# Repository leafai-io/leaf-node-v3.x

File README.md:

# Leaf Node 3.1

Leaf AI is an independent, open-source project. If you find it useful, you can support its continued development at [Leaf AI Support](https://leafai.io/support.html).

The Leaf Node is an open-source environmental 
monitoring and control device built on the 
ESP32-S3. It reads sensor data, publishes it 
over MQTT, and can trigger actuators — allowing 
you to monitor conditions and directly control 
connected devices such as lights, fans, pumps 
and valves. Configuration is handled wirelessly 
via BLE, making it a self-contained building 
block for precision agriculture and 
environmental monitoring and automation systems.

<!-- Hero image: replace the path below with your device photo -->
<!--  -->

---

## Philosophy

Leaf Node is built around one principle: **it should just work.** From first flash to live sensor data in minutes — simple enough for a grower to deploy in the field, open enough for a developer to extend and build on. No unnecessary complexity, no steep learning curve.

---

## Features

- **Multi-protocol sensor support** — I2C, RS485, SDI-12, OneWire on a single board
- **MQTT telemetry** — publishes sensor data and heartbeats, receives commands
- **OTA firmware updates** — triggered via MQTT command, no physical access needed
- **BLE provisioning** — initial Wi-Fi and MQTT setup from the companion app, no serial cable required
- **Scheduling** — DAC and actuator outputs can be programmed on a time-based schedule
- **Smart control** — MOSFET and relay outputs with duration-based switching
- **Node chaining** — UART-based daisy-chain for multi-node deployments
- **Watchdog & health monitoring** — automatic recovery with exponential backoff on sensor errors
- **Factory mode** — serial-console provisioning for production flashing

---

## Hardware

### Overview

| Component | Details |
|-----------|---------|
| MCU | ESP32-S3 |
| Status LED | WS2812B addressable RGB (v3) |
| RS485 | Half-duplex, DE/RE controlled |
| I2C | SDA GPIO8, SCL GPIO9 |
| SDI-12 | GPIO12 (shared with OneWire via hardware bridge) |
| OneWire | GPIO12 |
| Actuators | MOSFET (GPIO36), Relay (GPIO38), DAC (MCP4725 via I2C) |
| PWM | GPIO2 (1 kHz, 10-bit) + MOSFET gate (5 kHz, 10-bit) |

### Supported Sensors

| Sensor | Interface | Wiring | Measurement |
|--------|-----------|--------|-------------|
| SHT31  | I2C (0x44) | +3.3V · GND · SDA · SCL | Temperature, Humidity |
| EZO pH | I2C (0x63) | +3.3V · GND · SDA · SCL | pH |
| EZO EC | I2C (0x64) | +3.3V · GND · SDA · SCL | Electrical Conductivity |
| TEROS 12 | SDI-12 | +3.3V · GND · SDI-12 | Soil moisture, temperature, EC |
| DS18B20 | OneWire | +3.3V · GND · Need Modification | Temperature |
| SLT5007 | RS485 | +3.3V · GND · A · B | VWC, Bulk EC, Soil temperature, Pore EC |
| CWT-PSS | RS485 | +12V · GND · A · B | PAR (Photosynthetically Active Radiation) |
| LEAFTHSN | RS485 | +12V · GND · A · B | Leaf wetness, Leaf temperature |
| CWT-SoilTHS | RS485 | +12V · GND · A · B | VWC, Soil temperature |
| CWT-THXXS | RS485 | +12V · GND · A · B | Air temperature, Humidity, VPD |

### Actuators

| Actuator | GPIO / Interface | Wiring | Typical Use |
|----------|-----------------|--------|-------------|
| MOSFET | GPIO36 | +12V · -PWR | Pumps, fans, DC loads |
| Relay | GPIO38 | COM · NO · NC | AC/DC switching, high-current loads |
| DAC (MCP4725) | I2C (0x60) | 0-10V · GND | Analog 0–5 V output (e.g. dosing pumps) |
| PWM | GPIO2 | IO2 · GND | Variable speed / dimming control |

### PCB & Enclosure

- KiCad project: [hardware/pcb/kiCad/](hardware/pcb/kiCad/)
- Enclosure STL/STEP files: [hardware/enclosure/](hardware/enclosure/)
---

## Getting Started

### Option A — Web Flasher (recommended)

No toolchain required. Works directly in Chrome/Edge.

1. **Get the hardware** — order a ready-to-use Leaf Node at [Build Your Leaf Node](https://leafai.io/build-node.html), or fabricate your own PCB from the [KiCad files](hardware/pcb/kiCad/)
2. Open the **[Leaf AI Firmware Flasher](https://leafai.io/firmware-flasher.html)** and follow the on-screen steps
3. Open the Leaf AI app, tap **Add Device**, and provision Wi-Fi via BLE

That's it — the node connects to the Leaf AI backend and starts publishing sensor data.

> A free Leaf AI account is required to use the app. Sign up directly in the Leaf AI app.

---

### Option B — Build from source (PlatformIO)

For developers who want to modify or extend the firmware.

**Prerequisites:** [PlatformIO](https://platformio.org/) (CLI or VS Code extension)

#### 1. Assemble the hardware

Fabricate the PCB from the files in [hardware/pcb/](hardware/pcb/) and wire your sensors according to the pin table above.

#### 2. Flash the firmware

> **First flash:** Use the **[Leaf AI Firmware Flasher](https://leafai.io/firmware-flasher.html)** for the initial flash. It writes a compatible serial number to the device that is required for communication with the Leaf AI app. Subsequent builds can be uploaded via PlatformIO.

```bash
git clone https://github.com/leafai-io/leaf-node-v3.1.git
cd leaf-node-v3.1
pio run --target upload
```

Monitor serial output (115200 baud):

```bash
pio device monitor
```

#### 3. Provision via BLE

Open the Leaf AI app, tap **Add Device**, and follow the on-screen steps to configure Wi-Fi and link your account.

---

## Using with the App

Once your Leaf Node is provisioned, open the Leaf AI app to view live sensor readings, configure schedules, and control actuators — all from your phone.

---

## License

This project uses two open-source licences depending on what you are working with:

| Component | Licence |
|-----------|---------|
| Firmware / Software | [GNU AGPL-3.0](licenses/LICENSE-SOFTWARE) |
| Hardware (PCB, enclosure) | [CERN-OHL-S v2](licenses/LICENSE-HARDWARE) |

**Software (AGPL-3.0):** You can use, modify, and distribute the firmware freely, but any modified version you run as a networked service must also be released under the same licence.

**Hardware (CERN-OHL-S v2):** You can study, modify, and manufacture the hardware freely, but any modified design you distribute or produce must be released under the same licence with complete source files.

**If you create a fork, we'd love to hear about it.** Open an issue or send us a message so we can showcase your project and potentially integrate useful improvements.

---

## Support

Leaf AI is an independent, open-source project. If you find it useful, you can support its continued development at [Leaf AI Support](https://leafai.io/support.html).

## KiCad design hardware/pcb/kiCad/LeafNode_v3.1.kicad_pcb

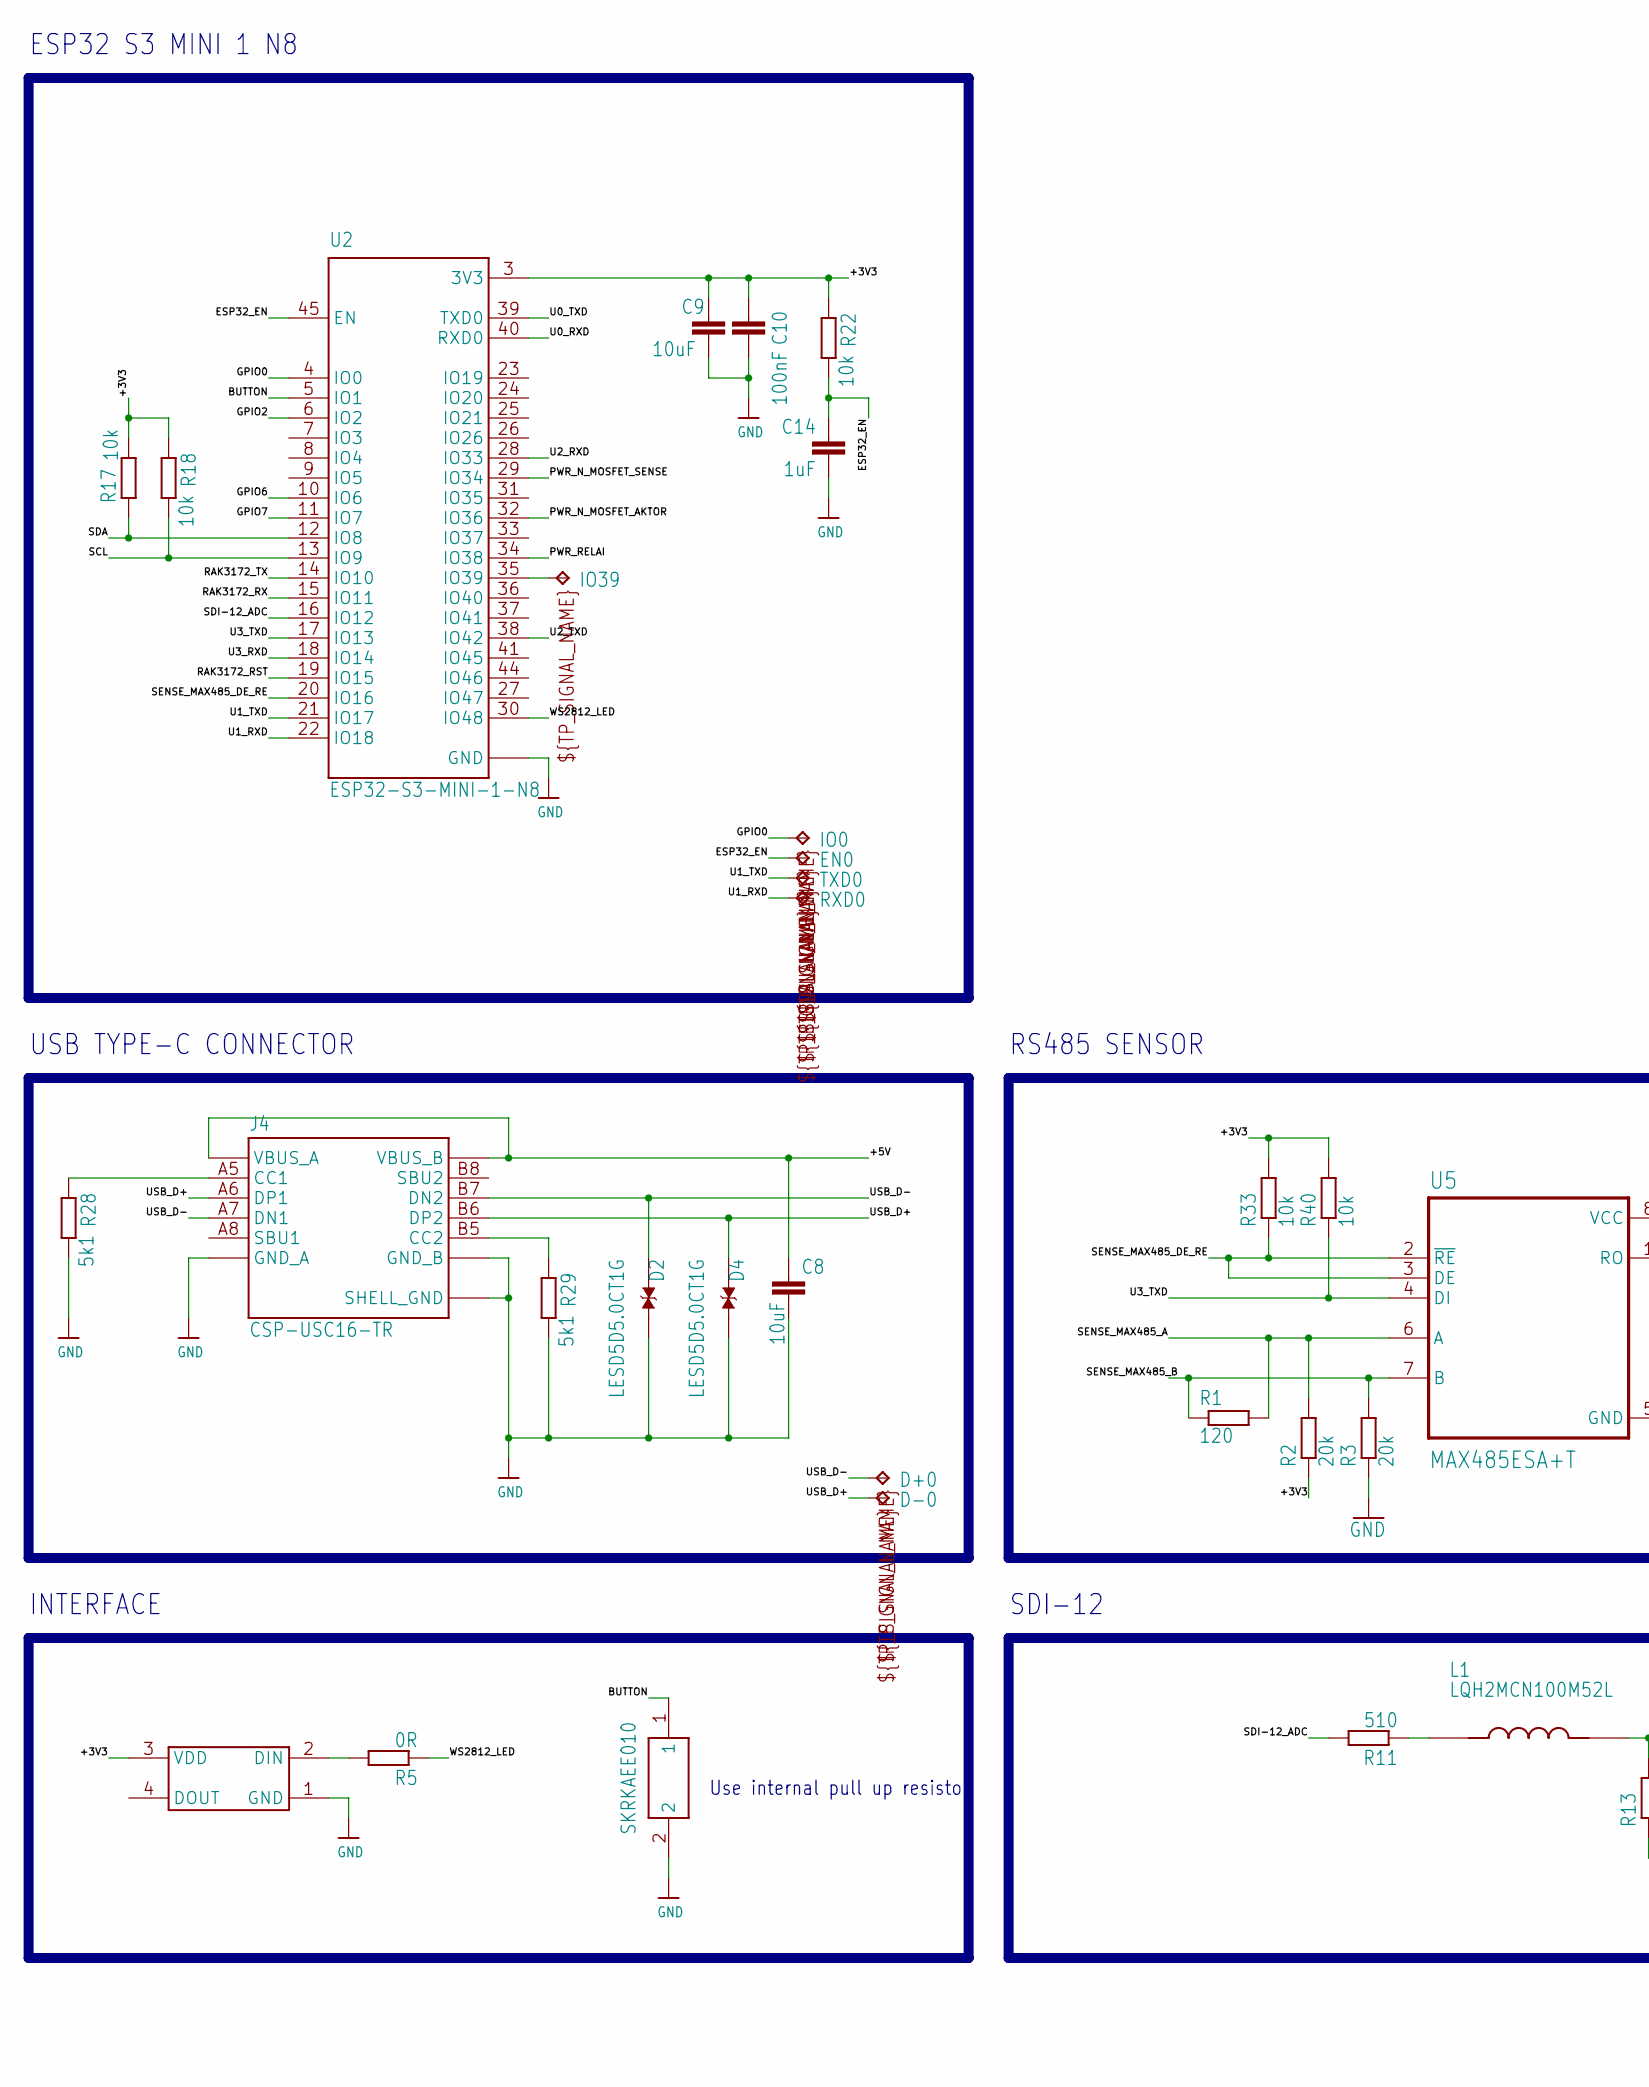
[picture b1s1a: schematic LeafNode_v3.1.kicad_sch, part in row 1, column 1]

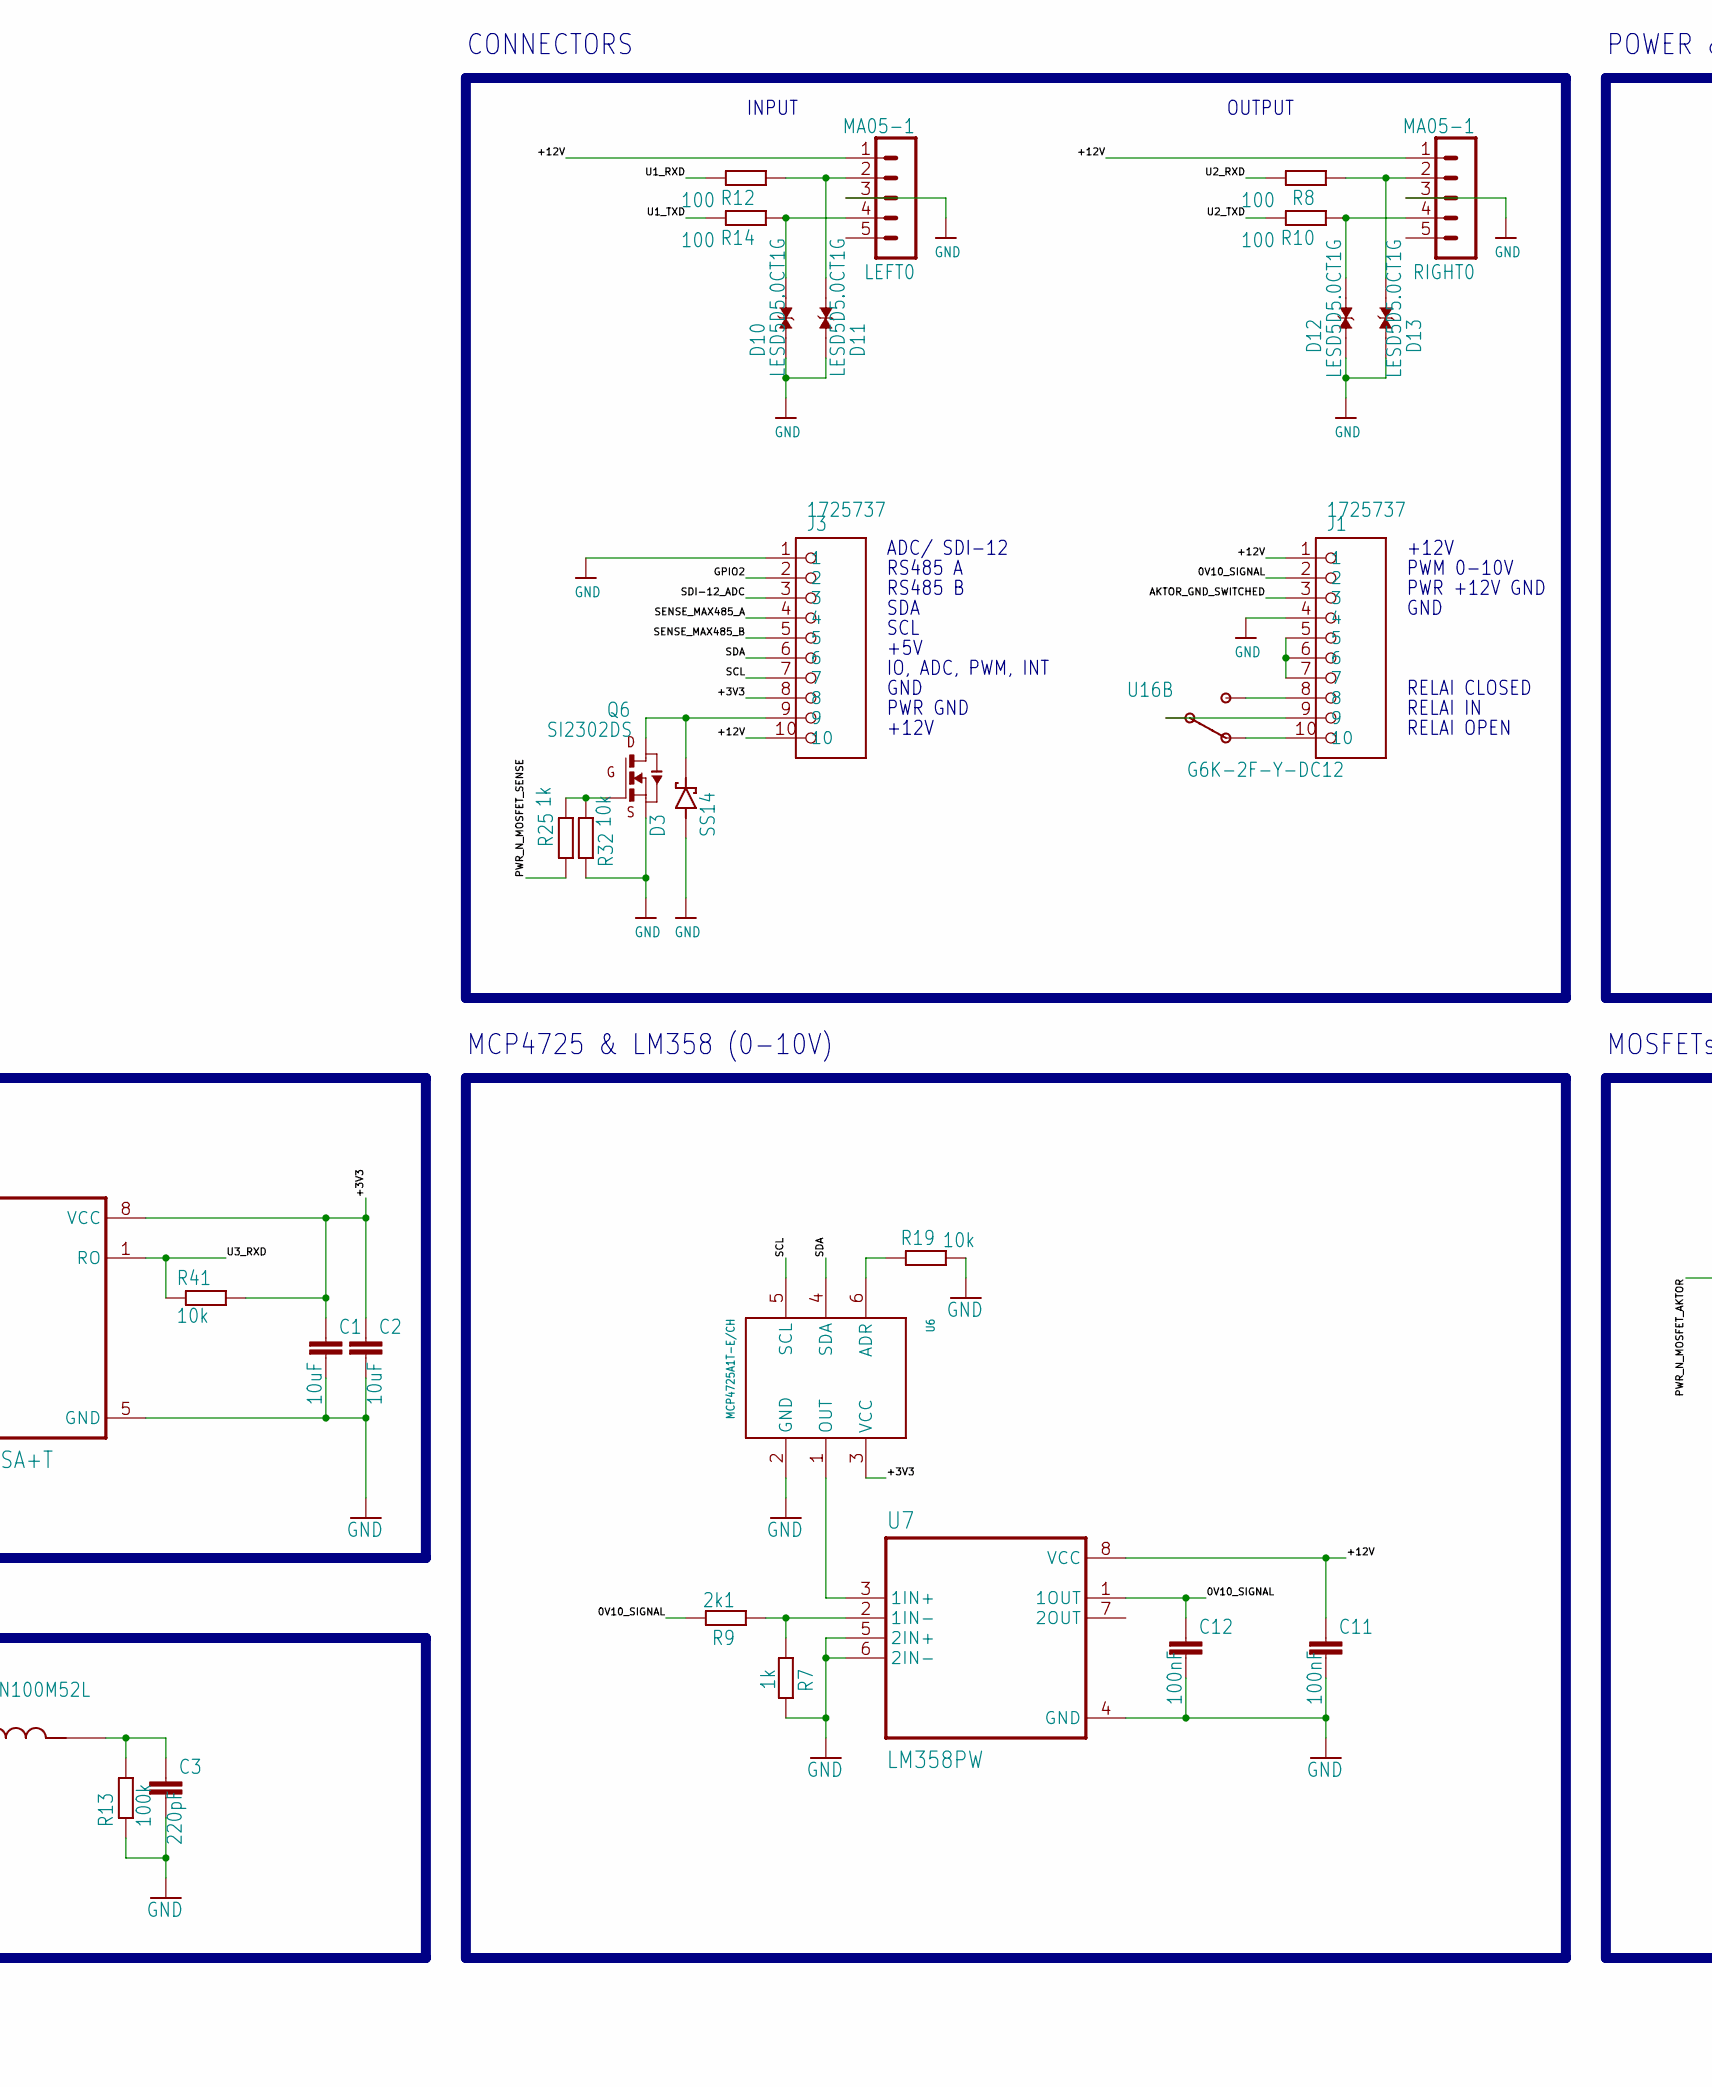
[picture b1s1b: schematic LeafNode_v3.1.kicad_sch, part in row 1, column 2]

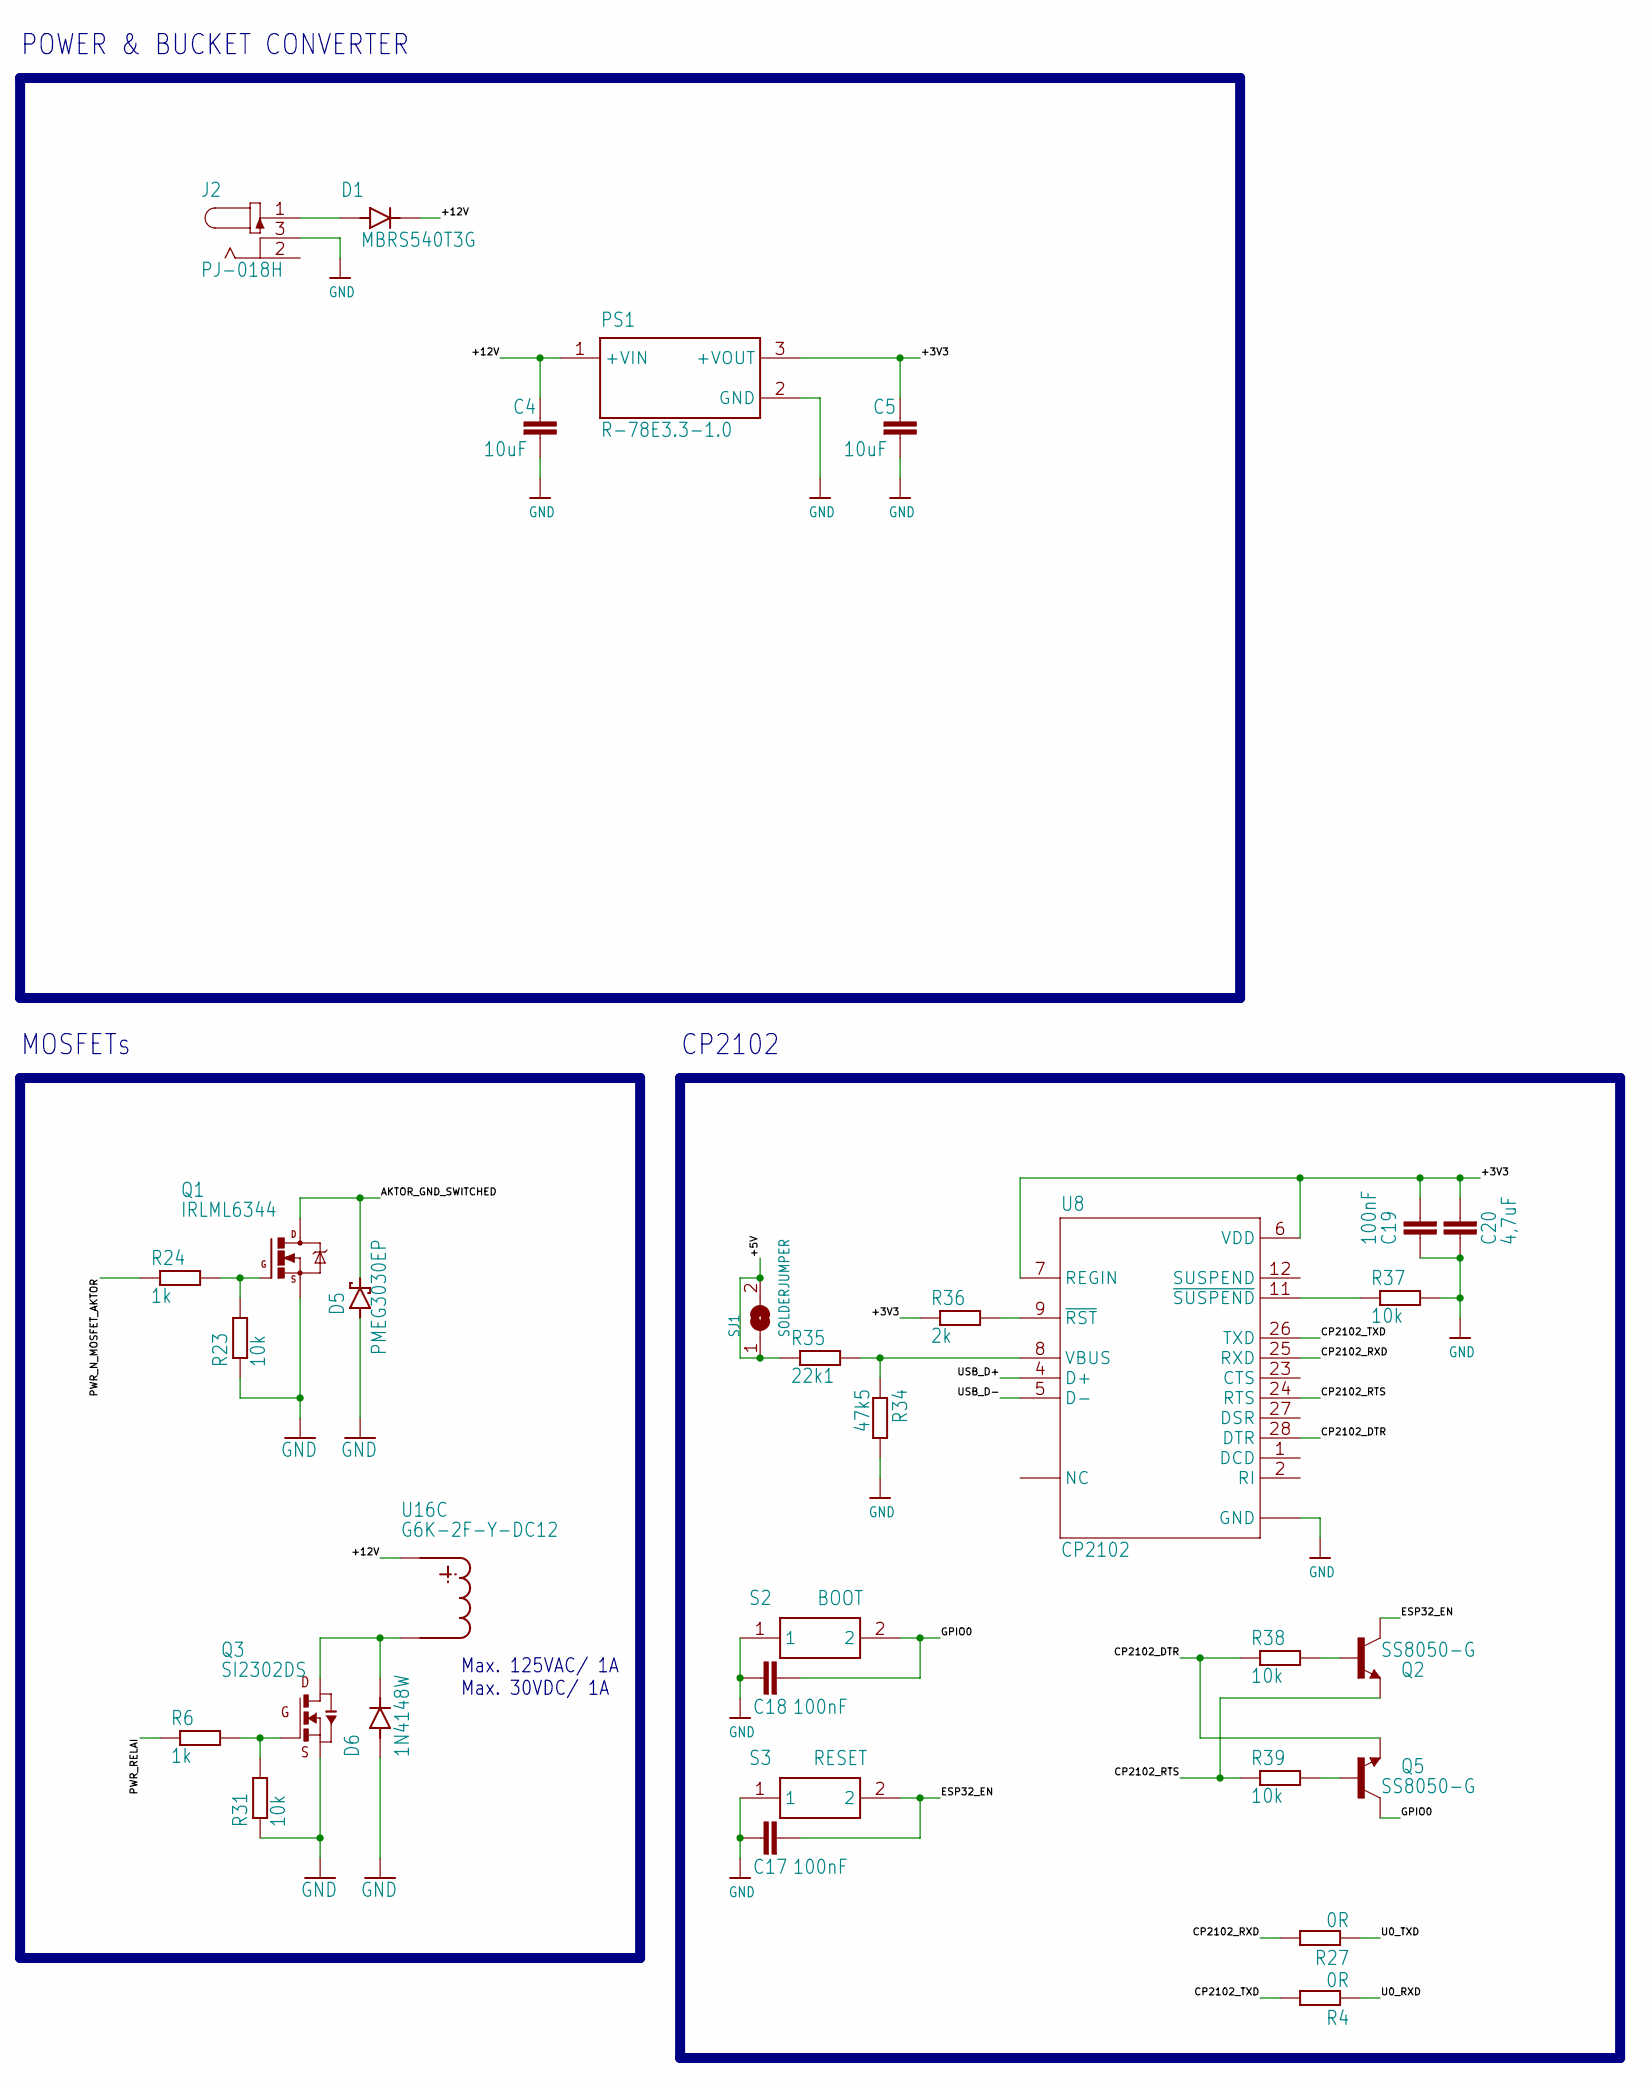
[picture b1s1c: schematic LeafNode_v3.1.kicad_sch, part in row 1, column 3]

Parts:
C1, C2, C4, C5, C8, C9: 10uF; C0603
C3: 220pF; C0603
C10, C11, C12, C17, C18, C19: 100nF; C0603
C14: 1uF; C0603
C20: 4,7uF; C0603
D1: MBRS540T3G; DIOM7959X261N
D2, D4, D10, D11, D12, D13: LESD5D5.0CT1G; TVS_LESD5D5.0CT1G
D3: SS14; DIOM4325X250N
D5: PMEG3030EP; SOD_128
D6: 1N4148W; SODFL3816X120N
D7: SK68XXMINI-HS; 3535
D+0: TPTP13R; TP13R
D-0: TPTP13R; TP13R
EN0: TPTP13R; TP13R
IO0, IO39: TPTP13R; TP13R
J1, J3: 1725737; PHOENIX_1725737
J2: PJ-018H; CUI_PJ-018H
J4: CSP-USC16-TR; VALCON_CSP-USC16-TR
L1: LQH2MCN100M52L; IND_LQH2MCN100M52L
LEFT0: MA05-1
PS1: R-78E3.3-1.0; CONV_R-78E3.3-1.0
Q1: IRLML6344; SOT23
Q2, Q5: SS8050-G; TRANS_SS8050-G
Q3, Q6: SI2302DS; SOT23-3_TO-236AB
R1: 120; R0402
R2, R3: 20k; R0402
R4, R5, R27: 0R; R0402
R6, R7, R24, R25: 1k; R0402
R8, R10, R12, R14: 100; R0402
R9: 2k1; R0402
R11: 510; R0402
R13: 100k; R0402
R17, R18, R19, R22, R23, R31, R32, R33, R37, R38, R39, R40, R41: 10k; R0402
R28, R29: 5k1; R0402
R34: 47k5; R0402
R35: 22k1; R0402
R36: 2k; R0402
RIGHT0: MA05-1
RXD0: TPTP13R; TP13R
S1: SKRKAEE010; SKRK
S2: BOOT; SKRK
S3: RESET; SKRK
SJ1: SOLDERJUMPER; SOLDERJUMPER_ARROW_NOPASTE
TXD0: TPTP13R; TP13R
U2: ESP32-S3-MINI-1-N8; XCVR_ESP32-S3-MINI-1-N8
U5: MAX485ESA+T; SOIC127P600X175-8N
U6: MCP4725A1T-E/CH; SOT23-6
U7: LM358PW; SOP65P640X120-8N
U8: CP2102; QFN50P500X500X100-29N
U16: G6K-2F-Y-DC12; G6K

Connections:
0V10_SIGNAL: C12.1, J1.2, R9.2, U7.1 (1OUT)
+3V3: C1.1, C2.1, C5.1, C9.1, C10.1, C19.2, C20.2, D7.3 (VDD), J3.8, PS1.3 (+VOUT), R2.1, R17.1, R18.2, R22.2, R33.2, R36.1, R40.2, R41.2, U2.3 (3V3), U5.8 (VCC), U6.3 (VCC), U8.6 (VDD), U8.7 (REGIN)
+5V: C8.1, J4.A4 (VBUS_A), J4.A9 (VBUS_A), J4.B4 (VBUS_B), J4.B9 (VBUS_B), R35.1, SJ1.1, SJ1.2
+12V: C4.1, C11.1, D1.1 (C), J1.1, J3.10, LEFT0.1, PS1.1 (+VIN), RIGHT0.1, U7.8 (VCC), U16.1 (COIL+)
AKTOR_GND_SWITCHED: D5.C, J1.3, Q1.3 (D)
BUTTON: S1.1, U2.5 (IO1)
CP2102_DTR: Q5.2 (E), R38.1, U8.28 (DTR)
CP2102_RTS: Q2.2 (E), R39.1, U8.24 (RTS)
CP2102_RXD: R27.2, U8.25 (RXD)
CP2102_TXD: R4.2, U8.26 (TXD)
ESP32_EN: C14.1, C17.2, EN0.TP, Q2.3 (C), R22.1, S3.2, U2.45 (EN)
GND: C1.2, C2.2, C3.2, C4.2, C5.2, C8.2, C9.2, C10.2, C11.2, C12.2, C14.2, C17.1, C18.1, C19.1, C20.1, D2.2, D3.A, D4.2, D5.A, D6.A, D7.1 (GND), D10.1, D11.1, D12.2, D13.2, J1.4, J2.3, J3.1, J4.A1 (GND_A), J4.A12 (GND_A), J4.B1 (GND_B), J4.B12 (GND_B), J4.S1 (SHELL_GND), J4.S2 (SHELL_GND), J4.S3 (SHELL_GND), J4.S4 (SHELL_GND), LEFT0.3, PS1.2 (GND), Q1.2 (S), Q3.2 (S), Q6.2 (S), R3.1, R7.2, R13.1, R19.1, R23.1, R28.1, R29.1, R31.1, R32.1, R34.2, R37.2, RIGHT0.3, S1.2, S2.1, S3.1, U2.1 (GND), U2.2 (GND), U2.42 (GND), U2.43 (GND), U2.46 (GND), U2.47 (GND), U2.48 (GND), U2.49 (GND), U2.50 (GND), U2.51 (GND), U2.52 (GND), U2.53 (GND), U2.54 (GND), U2.55 (GND), U2.56 (GND), U2.57 (GND), U2.58 (GND), U2.59 (GND), U2.60 (GND), U2.61 (GND), U2.61_1 (GND), U2.61_2 (GND), U2.61_3 (GND), U2.61_4 (GND), U2.61_5 (GND), U2.61_6 (GND), U2.61_7 (GND), U2.61_8 (GND), U2.62 (GND), U2.63 (GND), U2.64 (GND), U2.65 (GND), U5.5 (GND), U6.2 (GND), U7.4 (GND), U7.5 (2IN+), U7.6 (2IN-), U8.3 (GND), U8.29 (GND)
GPIO0: C18.2, IO0.TP, Q5.3 (C), S2.2, U2.4 (IO0)
GPIO2: J3.2, U2.6 (IO2)
GPIO6: U2.10 (IO6)
GPIO7: U2.11 (IO7)
unnamed: U6.1 (OUT), U7.3 (1IN+)
unnamed: R7.1, R9.1, U7.2 (1IN-)
unnamed: J1.5, J1.6, J1.7
unnamed: R19.2, U6.6 (ADR)
unnamed: D7.2 (DIN), R5.2
unnamed: R37.1, U8.11 (~SUSPEND)
unnamed: L1.1, R11.1
unnamed: C3.1, L1.2, R13.2
unnamed: D3.C (K), J3.9, Q6.3 (D)
unnamed: Q6.1 (G), R25.2, R32.2
unnamed: R36.2, U8.9 (~RST)
unnamed: R34.1, R35.2, U8.8 (VBUS)
unnamed: IO39.TP, U2.35 (IO39)
unnamed: Q2.1 (B), R38.2
unnamed: Q5.1 (B), R39.2
unnamed: J1.9, U16.3 (COMMON)
unnamed: Q1.1 (G), R23.2, R24.2
unnamed: J1.8, U16.4 (CONTACT_NO)
unnamed: J1.10, U16.2 (CONTACT_NC)
unnamed: D6.C (K), Q3.3 (D), U16.8 (COIL-)
unnamed: Q3.1 (G), R6.2, R31.2
unnamed: D1.2 (A), J2.1
unnamed: J4.A5 (CC1), R28.2
unnamed: D11.2, LEFT0.2, R12.1
unnamed: J4.B5 (CC2), R29.2
unnamed: D10.2, LEFT0.4, R14.1
unnamed: D13.1, R8.1, RIGHT0.2
unnamed: D12.1, R10.1, RIGHT0.4
PWR_N_MOSFET_AKTOR: R24.1, U2.32 (IO36)
PWR_N_MOSFET_SENSE: R25.1, U2.29 (IO34)
PWR_RELAI: R6.1, U2.34 (IO38)
RAK3172_RST: U2.19 (IO15)
RAK3172_RX: U2.15 (IO11)
RAK3172_TX: U2.14 (IO10)
SCL: J3.7, R18.1, U2.13 (IO9), U6.5 (SCL)
SDA: J3.6, R17.2, U2.12 (IO8), U6.4 (SDA)
SDI-12_ADC: J3.3, R11.2, U2.16 (IO12)
SENSE_MAX485_A: J3.4, R1.2, R2.2, U5.6 (A)
SENSE_MAX485_B: J3.5, R1.1, R3.2, U5.7 (B)
SENSE_MAX485_DE_RE: R33.1, U2.20 (IO16), U5.2 (~RE), U5.3 (DE)
U0_RXD: R4.1, U2.40 (RXD0)
U0_TXD: R27.1, U2.39 (TXD0)
U1_RXD: R12.2, RXD0.TP, U2.22 (IO18)
U1_TXD: R14.2, TXD0.TP, U2.21 (IO17)
U2_RXD: R8.2, U2.28 (IO33)
U2_TXD: R10.2, U2.38 (IO42)
U3_RXD: R41.1, U2.18 (IO14), U5.1 (RO)
U3_TXD: R40.1, U2.17 (IO13), U5.4 (DI)
USB_D+: D4.1, D-0.TP, J4.A6 (DP1), J4.B6 (DP2), U8.4 (D+)
USB_D-: D2.1, D+0.TP, J4.A7 (DN1), J4.B7 (DN2), U8.5 (D-)
WS2812_LED: R5.1, U2.30 (IO48)

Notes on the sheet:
MOSFETs
RELAI IN
+12V
PWR +12V GND
PWR GND
RS485 SENSOR
Use internal pull up resistor
SDA
MCP4725 & LM358 (0-10V)
+5V
RS485 B
RELAI CLOSED
GND
OUTPUT
SDI-12
ESP32 S3 MINI 1 N8
CP2102
CONNECTORS
INTERFACE
RELAI OPEN
POWER & BUCKET CONVERTER
PWM 0-10V
USB TYPE-C CONNECTOR
Max. 125VAC/ 1A Max. 30VDC/ 1A
IO, ADC, PWM, INT
ADC/ SDI-12
INPUT
RS485 A
SCL

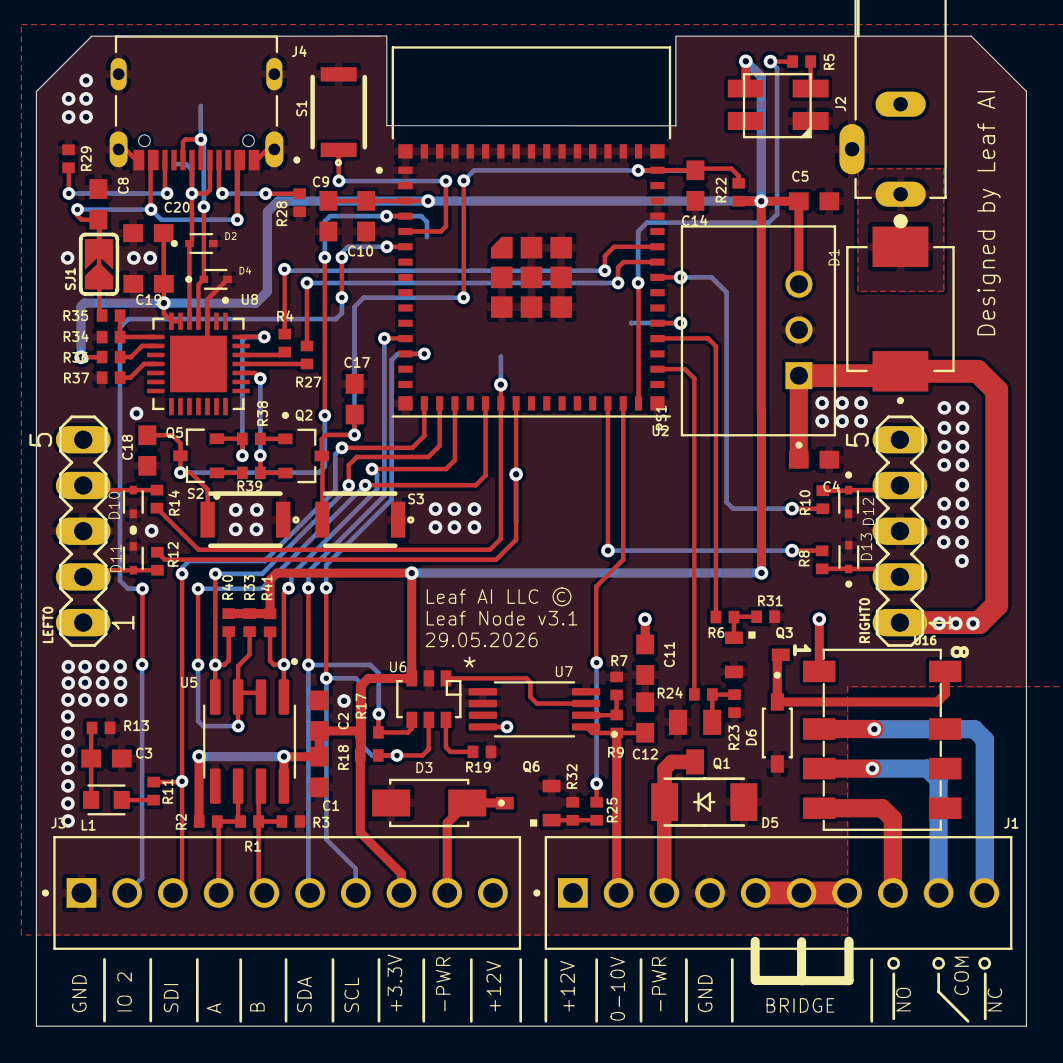
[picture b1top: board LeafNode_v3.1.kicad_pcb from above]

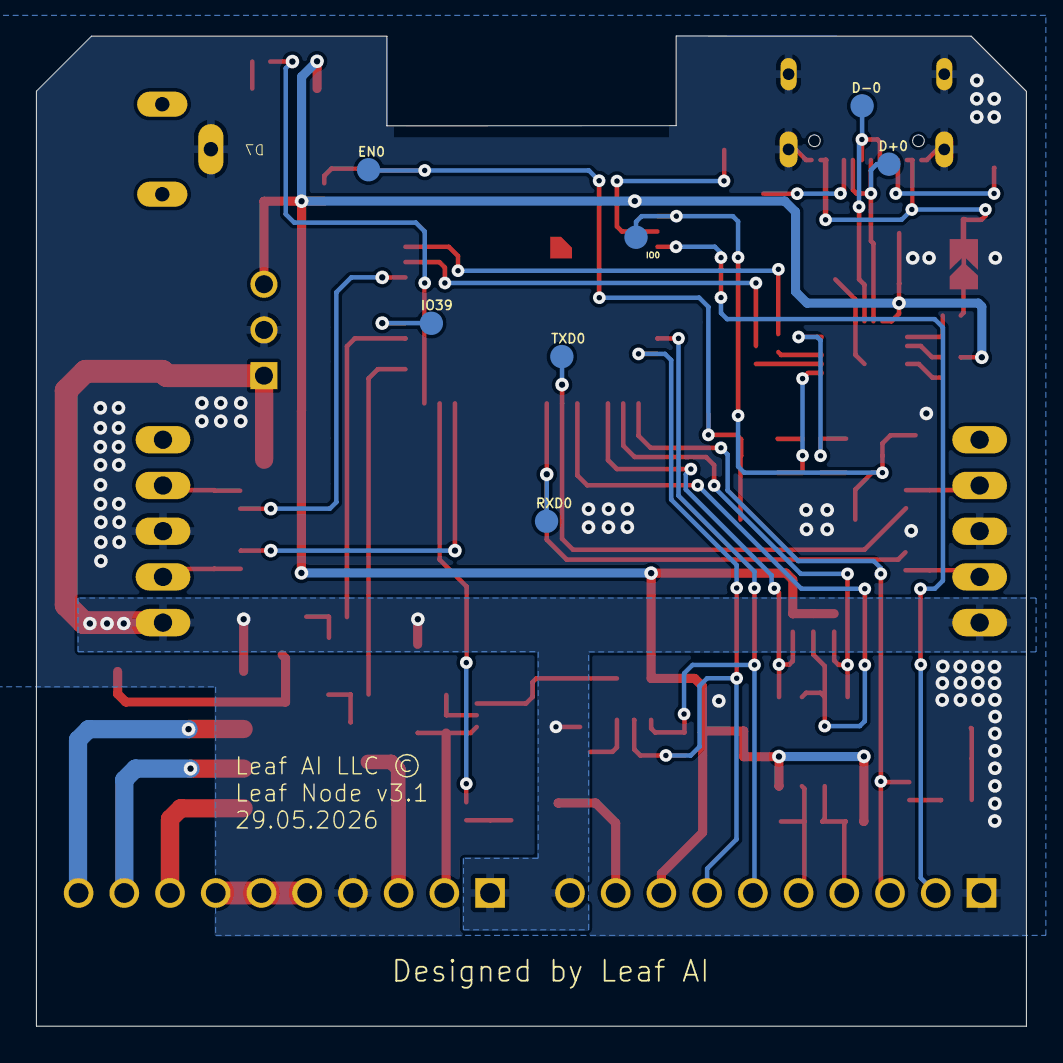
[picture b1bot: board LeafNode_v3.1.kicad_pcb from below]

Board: 2 copper layers, 55.0 x 55.0 mm, 91 parts (7 on the bottom side), 62 nets.

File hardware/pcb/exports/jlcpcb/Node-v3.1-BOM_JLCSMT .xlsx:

Tabelle 1
Comment | Designator | Footprint | JLCPCB Part # (optional)
0R | R4, R5, R27 | R0402 | C21376
100k | R13 | R0402 | C25530
100nF | C10, C11, C12, C17, C18, C19 | C0603 | C1590
10k | R17, R18, R19, R22, R23, R31, R32, R33, R37, R38, R39, R40, R41 | R0402 | C25531
10uF | C1, C2, C4, C5, C8, C9 | C0603 | C1691
120R | R1 | R0402 | C25079
1725737 | J1, J3 | PHOENIX_1725737 | C2922605
1N4148W | D6 | SODFL3816X120N | C2099
1k | R6, R7, R24, R25 | R0402 | C11702
1uF | C14 | C0603 | C1592
20k | R2, R3 | R0402 | C25545
220pF | C3 | C0603 | C1603
22k1 | R35 | R0402 | C163478
PZ2.54-1*5-FWZ | LEFT | Push-Pull,P=2.54mm | C5224018
HX PM2.54-1x5P WC-Y | RIGHT | Push-Pull,P=2.54mm | C22438146
2k | R36 | R0402 | C25552
2k1 | R9 | R0402 | C25877
4,7uF | C20 | C0603 | C71631
47k5 | R34 | R0402 | C137974
100R | R8, R10, R12, R14 | R0402 | C100570
510R | R11 | R0402 | C1119
5k1 | R28, R29 | R0402 | C100665
SKRKAEE020 | S1, S2, S3 | SKRK | C115357
CP2102 | U8 | QFN50P500X500X100-29N | C6568
CSP-USC16-TR | J4 | VALCON_CSP-USC16-TR | C20883031
ESP32-S3-MINI-1-N8 | U2 | XCVR_ESP32-S3-MINI-1-N8 | C2913206
G6K-2F-Y-DC12 | U16 | G6K | C397194
IRLML6344 | Q1 | SOT23 | C5364313
LESD5D5.0CT1G | D2, D4, D10, D11, D12, D13 | TVS_LESD5D5.0CT1G | C383211
LM358PW | U7 | SOP65P640X120-8N | C7951
LQH2MCN100M52L | L1 | IND_LQH2MCN100M52L | C703109
MAX485ESA+T | U5 | SOIC127P600X175-8N | C2687394
MBRS540T3G | D1 | DIOM7959X261N | C31849
MCP4725A1T-E/CH | U6 | SOT23-6 | C61423
R-78E3.3-1.0 | PS1 | CONV_R-78E3.3-1.0 | C53454360
PJ-018H | J2 | CUI_PJ-018H | C3095066
PMEG3030EP | D5 | SOD_128 | C255587
SI2302DS | Q3, Q6 | SOT23-3/TO-236AB | C5310967
SS14 | D3 | DIOM4325X250N | SS14
SS8050-G | Q2, Q5 | TRANS_SS8050-G | C164885
SK68XXMINI-HS | D7 | 3535 | C9900024290

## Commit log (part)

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2026-06-15 Clean schematic
2026-06-15 added .history to gitignore
2026-06-23 Just updated the readme
